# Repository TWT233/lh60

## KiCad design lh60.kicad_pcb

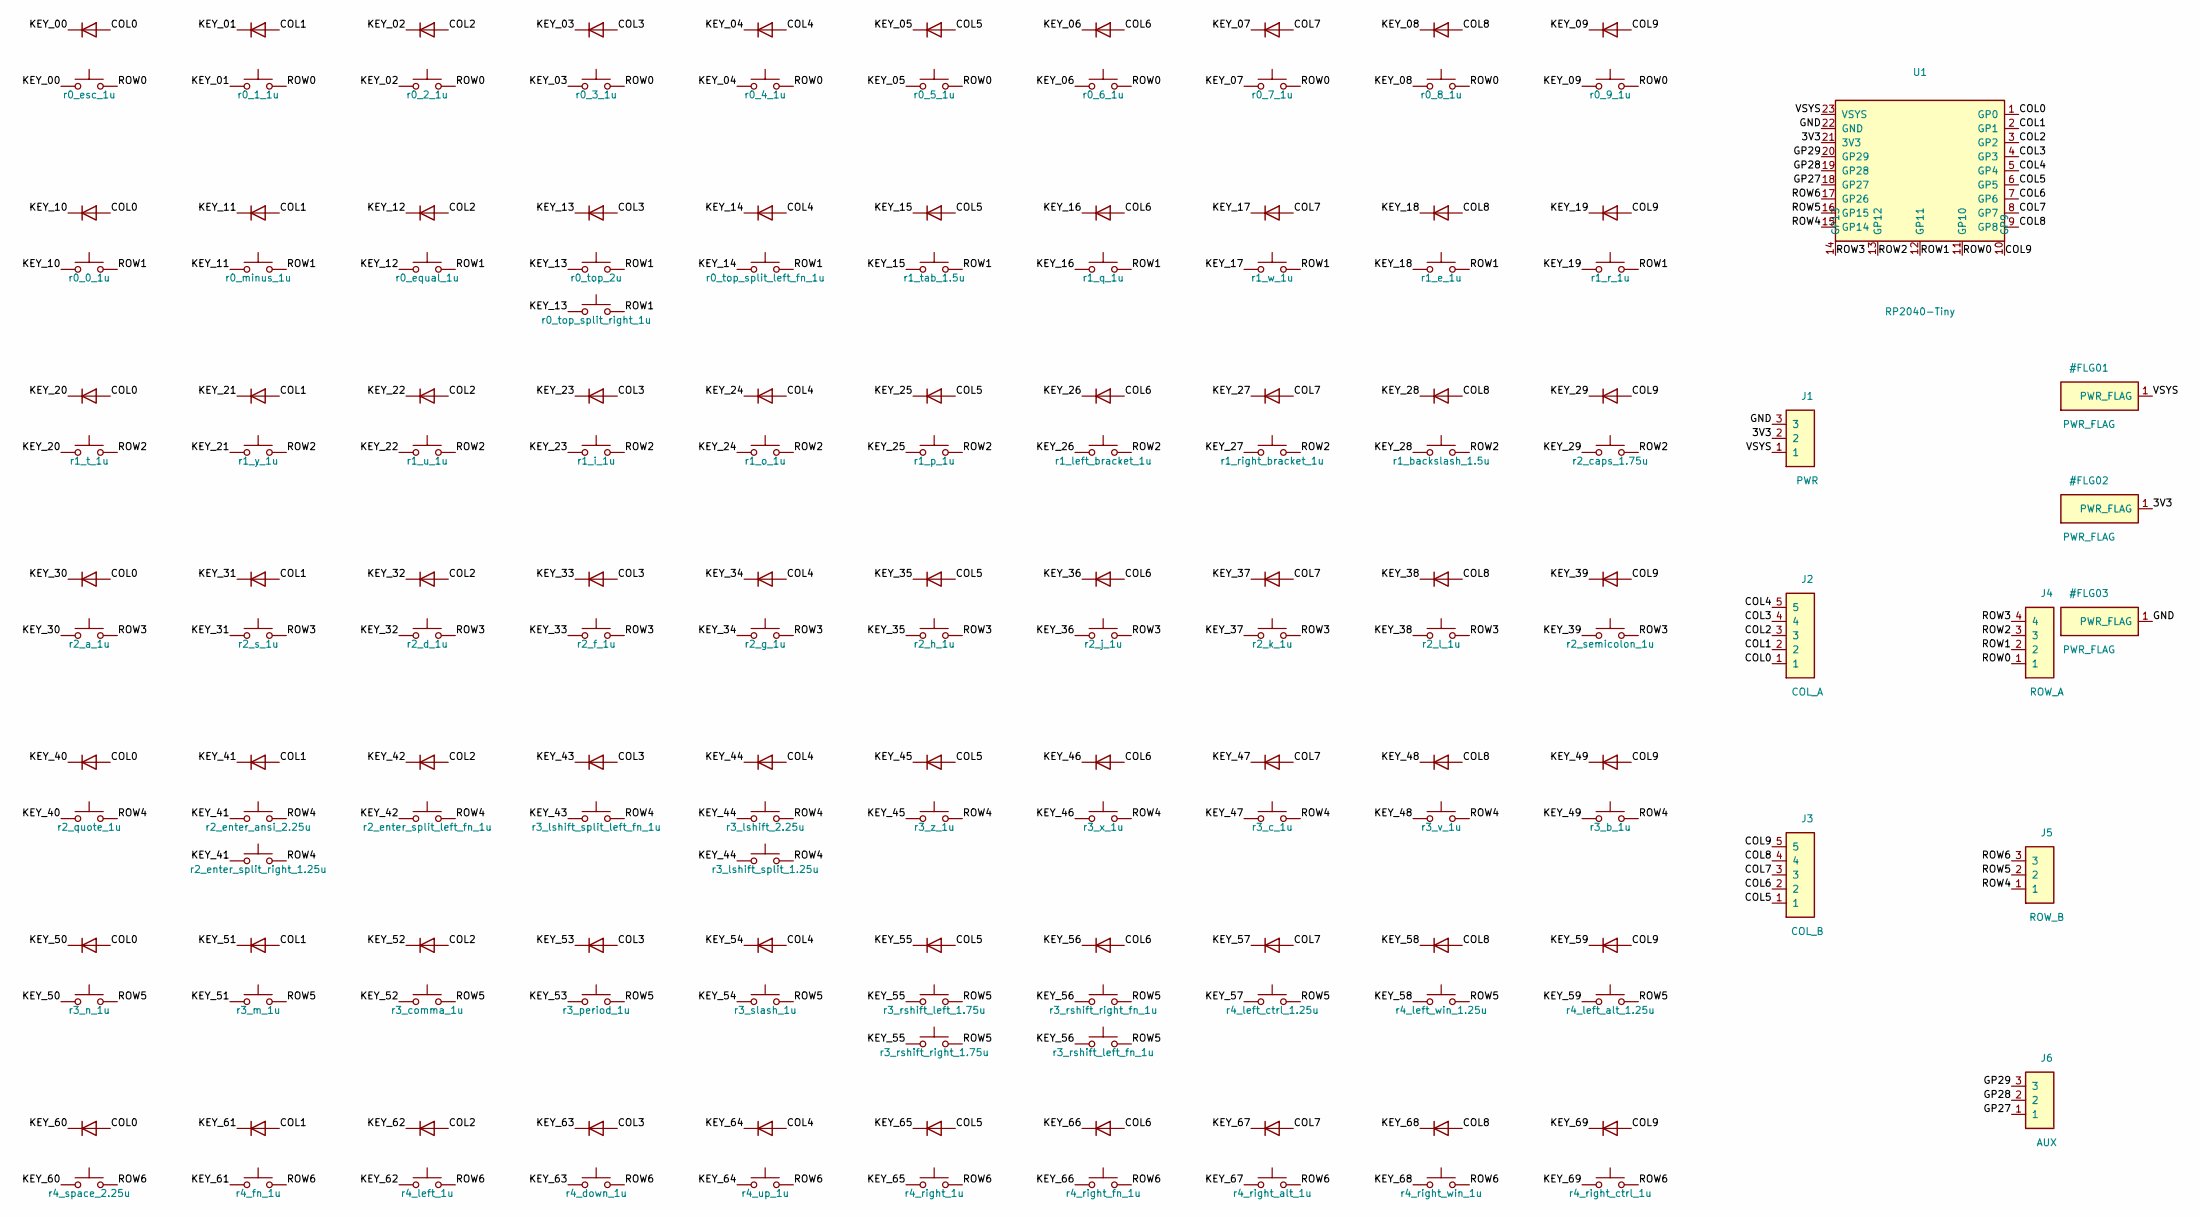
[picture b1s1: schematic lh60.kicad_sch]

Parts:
D1, D2, D3, D4, D5, D6, D7, D8, D9, D10, D11, D12, D13, D14, D15, D16, D17, D18, D19, D20, D21, D22, D23, D24, D25, D26, D27, D28, D29, D30, D31, D32, D33, D34, D35, D36, D37, D38, D39, D40, D41, D42, D43, D44, D45, D46, D47, D48, D49, D50, D51, D52, D53, D54, D55, D56, D57, D58, D59, D60, D61, D62, D63, D64, D65, D66, D67, D68, D69, D70: 1N4148WS; D_SOD-323_Bottom
J1: PWR; PinHeader_1x03_P2.54mm_Vertical
J2: COL_A; PinHeader_1x05_P2.54mm_Vertical
J3: COL_B; PinHeader_1x05_P2.54mm_Vertical
J4: ROW_A; PinHeader_1x04_P2.54mm_Vertical
J5: ROW_B; PinHeader_1x03_P2.54mm_Vertical
J6: AUX; PinHeader_1x03_P2.54mm_Vertical
SW1: r0_esc_1u; Gateron-LP-or-ChocV1-Hotswap-Socket-1U
SW2: r0_1_1u; Gateron-LP-or-ChocV1-Hotswap-Socket-1U
SW3: r0_2_1u; Gateron-LP-or-ChocV1-Hotswap-Socket-1U
SW4: r0_3_1u; Gateron-LP-or-ChocV1-Hotswap-Socket-1U
SW5: r0_4_1u; Gateron-LP-or-ChocV1-Hotswap-Socket-1U
SW6: r0_5_1u; Gateron-LP-or-ChocV1-Hotswap-Socket-1U
SW7: r0_6_1u; Gateron-LP-or-ChocV1-Hotswap-Socket-1U
SW8: r0_7_1u; Gateron-LP-or-ChocV1-Hotswap-Socket-1U
SW9: r0_8_1u; Gateron-LP-or-ChocV1-Hotswap-Socket-1U
SW10: r0_9_1u; Gateron-LP-or-ChocV1-Hotswap-Socket-1U
SW11: r0_0_1u; Gateron-LP-or-ChocV1-Hotswap-Socket-1U
SW12: r0_minus_1u; Gateron-LP-or-ChocV1-Hotswap-Socket-1U
SW13: r0_equal_1u; Gateron-LP-or-ChocV1-Hotswap-Socket-1U
SW14: r0_top_2u; Gateron-LP-Hotswap-Socket-2U
SW15: r0_top_split_left_fn_1u; Gateron-LP-Hotswap-Socket-1U
SW16: r0_top_split_right_1u; Gateron-LP-Hotswap-Socket-1U
SW17: r1_tab_1.5u; Gateron-LP-or-ChocV1-Hotswap-Socket-1.5U
SW18: r1_q_1u; Gateron-LP-or-ChocV1-Hotswap-Socket-1U
SW19: r1_w_1u; Gateron-LP-or-ChocV1-Hotswap-Socket-1U
SW20: r1_e_1u; Gateron-LP-or-ChocV1-Hotswap-Socket-1U
SW21: r1_r_1u; Gateron-LP-or-ChocV1-Hotswap-Socket-1U
SW22: r1_t_1u; Gateron-LP-or-ChocV1-Hotswap-Socket-1U
SW23: r1_y_1u; Gateron-LP-or-ChocV1-Hotswap-Socket-1U
SW24: r1_u_1u; Gateron-LP-or-ChocV1-Hotswap-Socket-1U
SW25: r1_i_1u; Gateron-LP-or-ChocV1-Hotswap-Socket-1U
SW26: r1_o_1u; Gateron-LP-or-ChocV1-Hotswap-Socket-1U
SW27: r1_p_1u; Gateron-LP-or-ChocV1-Hotswap-Socket-1U
SW28: r1_left_bracket_1u; Gateron-LP-or-ChocV1-Hotswap-Socket-1U
SW29: r1_right_bracket_1u; Gateron-LP-or-ChocV1-Hotswap-Socket-1U
SW30: r1_backslash_1.5u; Gateron-LP-or-ChocV1-Hotswap-Socket-1.5U
SW31: r2_caps_1.75u; Gateron-LP-or-ChocV1-Hotswap-Socket-1.75U
SW32: r2_a_1u; Gateron-LP-or-ChocV1-Hotswap-Socket-1U
SW33: r2_s_1u; Gateron-LP-or-ChocV1-Hotswap-Socket-1U
SW34: r2_d_1u; Gateron-LP-or-ChocV1-Hotswap-Socket-1U
SW35: r2_f_1u; Gateron-LP-or-ChocV1-Hotswap-Socket-1U
SW36: r2_g_1u; Gateron-LP-or-ChocV1-Hotswap-Socket-1U
SW37: r2_h_1u; Gateron-LP-or-ChocV1-Hotswap-Socket-1U
SW38: r2_j_1u; Gateron-LP-or-ChocV1-Hotswap-Socket-1U
SW39: r2_k_1u; Gateron-LP-or-ChocV1-Hotswap-Socket-1U
SW40: r2_l_1u; Gateron-LP-or-ChocV1-Hotswap-Socket-1U
SW41: r2_semicolon_1u; Gateron-LP-or-ChocV1-Hotswap-Socket-1U
SW42: r2_quote_1u; Gateron-LP-or-ChocV1-Hotswap-Socket-1U
SW43: r2_enter_ansi_2.25u; Gateron-LP-Hotswap-Socket-2.25U
SW44: r2_enter_split_left_fn_1u; Gateron-LP-Hotswap-Socket-1U
SW45: r2_enter_split_right_1.25u; Gateron-LP-Hotswap-Socket-1.25U
SW46: r3_lshift_split_left_fn_1u; Gateron-LP-Hotswap-Socket-1U
SW47: r3_lshift_2.25u; Gateron-LP-Hotswap-Socket-2.25U
SW48: r3_lshift_split_1.25u; Gateron-LP-Hotswap-Socket-1.25U
SW49: r3_z_1u; Gateron-LP-or-ChocV1-Hotswap-Socket-1U
SW50: r3_x_1u; Gateron-LP-or-ChocV1-Hotswap-Socket-1U
SW51: r3_c_1u; Gateron-LP-or-ChocV1-Hotswap-Socket-1U
SW52: r3_v_1u; Gateron-LP-or-ChocV1-Hotswap-Socket-1U
SW53: r3_b_1u; Gateron-LP-or-ChocV1-Hotswap-Socket-1U
SW54: r3_n_1u; Gateron-LP-or-ChocV1-Hotswap-Socket-1U
SW55: r3_m_1u; Gateron-LP-or-ChocV1-Hotswap-Socket-1U
SW56: r3_comma_1u; Gateron-LP-or-ChocV1-Hotswap-Socket-1U
SW57: r3_period_1u; Gateron-LP-or-ChocV1-Hotswap-Socket-1U
SW58: r3_slash_1u; Gateron-LP-or-ChocV1-Hotswap-Socket-1U
SW60: r3_rshift_left_1.75u; Gateron-LP-Hotswap-Socket-1.75U
SW61: r3_rshift_right_fn_1u; Gateron-LP-Hotswap-Socket-1U
SW62: r3_rshift_left_fn_1u; Gateron-LP-Hotswap-Socket-1U
SW63: r3_rshift_right_1.75u; Gateron-LP-Hotswap-Socket-1.75U
SW64: r4_left_ctrl_1.25u; Gateron-LP-or-ChocV1-Hotswap-Socket-1.25U
SW65: r4_left_win_1.25u; Gateron-LP-or-ChocV1-Hotswap-Socket-1.25U
SW66: r4_left_alt_1.25u; Gateron-LP-or-ChocV1-Hotswap-Socket-1.25U
SW67: r4_space_2.25u; Gateron-LP-or-ChocV1-Hotswap-Socket-2.25U
SW68: r4_fn_1u; Gateron-LP-or-ChocV1-Hotswap-Socket-1U
SW69: r4_left_1u; Gateron-LP-or-ChocV1-Hotswap-Socket-1U
SW70: r4_down_1u; Gateron-LP-or-ChocV1-Hotswap-Socket-1U
SW71: r4_up_1u; Gateron-LP-or-ChocV1-Hotswap-Socket-1U
SW72: r4_right_1u; Gateron-LP-or-ChocV1-Hotswap-Socket-1U
SW73: r4_right_fn_1u; Gateron-LP-or-ChocV1-Hotswap-Socket-1U
SW74: r4_right_alt_1u; Gateron-LP-or-ChocV1-Hotswap-Socket-1U
SW75: r4_right_win_1u; Gateron-LP-or-ChocV1-Hotswap-Socket-1U
SW76: r4_right_ctrl_1u; Gateron-LP-or-ChocV1-Hotswap-Socket-1U
U1: RP2040-Tiny; MCU_RP2040-Tiny_SMD

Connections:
/3V3: J1.2, U1.21 (3V3)
/COL0: D1.2 (A), D11.2 (A), D21.2 (A), D31.2 (A), D41.2 (A), D51.2 (A), D61.2 (A), J2.1, U1.1 (GP0)
/COL1: D2.2 (A), D12.2 (A), D22.2 (A), D32.2 (A), D42.2 (A), D52.2 (A), D62.2 (A), J2.2, U1.2 (GP1)
/COL2: D3.2 (A), D13.2 (A), D23.2 (A), D33.2 (A), D43.2 (A), D53.2 (A), D63.2 (A), J2.3, U1.3 (GP2)
/COL3: D4.2 (A), D14.2 (A), D24.2 (A), D34.2 (A), D44.2 (A), D54.2 (A), D64.2 (A), J2.4, U1.4 (GP3)
/COL4: D5.2 (A), D15.2 (A), D25.2 (A), D35.2 (A), D45.2 (A), D55.2 (A), D65.2 (A), J2.5, U1.5 (GP4)
/COL5: D6.2 (A), D16.2 (A), D26.2 (A), D36.2 (A), D46.2 (A), D56.2 (A), D66.2 (A), J3.1, U1.6 (GP5)
/COL6: D7.2 (A), D17.2 (A), D27.2 (A), D37.2 (A), D47.2 (A), D57.2 (A), D67.2 (A), J3.2, U1.7 (GP6)
/COL7: D8.2 (A), D18.2 (A), D28.2 (A), D38.2 (A), D48.2 (A), D58.2 (A), D68.2 (A), J3.3, U1.8 (GP7)
/COL8: D9.2 (A), D19.2 (A), D29.2 (A), D39.2 (A), D49.2 (A), D59.2 (A), D69.2 (A), J3.4, U1.9 (GP8)
/COL9: D10.2 (A), D20.2 (A), D30.2 (A), D40.2 (A), D50.2 (A), D60.2 (A), D70.2 (A), J3.5, U1.10 (GP9)
/GND: J1.3, U1.22 (GND)
/GP27: J6.1, U1.18 (GP27)
/GP28: J6.2, U1.19 (GP28)
/GP29: J6.3, U1.20 (GP29)
/KEY_00: D1.1 (K), SW1.1
/KEY_01: D2.1 (K), SW2.1
/KEY_02: D3.1 (K), SW3.1
/KEY_03: D4.1 (K), SW4.1
/KEY_04: D5.1 (K), SW5.1
/KEY_05: D6.1 (K), SW6.1
/KEY_06: D7.1 (K), SW7.1
/KEY_07: D8.1 (K), SW8.1
/KEY_08: D9.1 (K), SW9.1
/KEY_09: D10.1 (K), SW10.1
/KEY_10: D11.1 (K), SW11.1
/KEY_11: D12.1 (K), SW12.1
/KEY_12: D13.1 (K), SW13.1
/KEY_13: D14.1 (K), SW14.1, SW16.1
/KEY_14: D15.1 (K), SW15.1
/KEY_15: D16.1 (K), SW17.1
/KEY_16: D17.1 (K), SW18.1
/KEY_17: D18.1 (K), SW19.1
/KEY_18: D19.1 (K), SW20.1
/KEY_19: D20.1 (K), SW21.1
/KEY_20: D21.1 (K), SW22.1
/KEY_21: D22.1 (K), SW23.1
/KEY_22: D23.1 (K), SW24.1
/KEY_23: D24.1 (K), SW25.1
/KEY_24: D25.1 (K), SW26.1
/KEY_25: D26.1 (K), SW27.1
/KEY_26: D27.1 (K), SW28.1
/KEY_27: D28.1 (K), SW29.1
/KEY_28: D29.1 (K), SW30.1
/KEY_29: D30.1 (K), SW31.1
/KEY_30: D31.1 (K), SW32.1
/KEY_31: D32.1 (K), SW33.1
/KEY_32: D33.1 (K), SW34.1
/KEY_33: D34.1 (K), SW35.1
/KEY_34: D35.1 (K), SW36.1
/KEY_35: D36.1 (K), SW37.1
/KEY_36: D37.1 (K), SW38.1
/KEY_37: D38.1 (K), SW39.1
/KEY_38: D39.1 (K), SW40.1
/KEY_39: D40.1 (K), SW41.1
/KEY_40: D41.1 (K), SW42.1
/KEY_41: D42.1 (K), SW43.1, SW45.1
/KEY_42: D43.1 (K), SW44.1
/KEY_43: D44.1 (K), SW46.1
/KEY_44: D45.1 (K), SW47.1, SW48.1
/KEY_45: D46.1 (K), SW49.1
/KEY_46: D47.1 (K), SW50.1
/KEY_47: D48.1 (K), SW51.1
/KEY_48: D49.1 (K), SW52.1
/KEY_49: D50.1 (K), SW53.1
/KEY_50: D51.1 (K), SW54.1
/KEY_51: D52.1 (K), SW55.1
/KEY_52: D53.1 (K), SW56.1
/KEY_53: D54.1 (K), SW57.1
/KEY_54: D55.1 (K), SW58.1
/KEY_55: D56.1 (K), SW60.1, SW63.1
/KEY_56: D57.1 (K), SW61.1, SW62.1
/KEY_57: D58.1 (K), SW64.1
/KEY_58: D59.1 (K), SW65.1
/KEY_59: D60.1 (K), SW66.1
/KEY_60: D61.1 (K), SW67.1
/KEY_61: D62.1 (K), SW68.1
/KEY_62: D63.1 (K), SW69.1
/KEY_63: D64.1 (K), SW70.1
/KEY_64: D65.1 (K), SW71.1
/KEY_65: D66.1 (K), SW72.1
/KEY_66: D67.1 (K), SW73.1
/KEY_67: D68.1 (K), SW74.1
/KEY_68: D69.1 (K), SW75.1
/KEY_69: D70.1 (K), SW76.1
/ROW0: J4.1, SW1.2, SW2.2, SW3.2, SW4.2, SW5.2, SW6.2, SW7.2, SW8.2, SW9.2, SW10.2, U1.11 (GP10)
/ROW1: J4.2, SW11.2, SW12.2, SW13.2, SW14.2, SW15.2, SW16.2, SW17.2, SW18.2, SW19.2, SW20.2, SW21.2, U1.12 (GP11)
/ROW2: J4.3, SW22.2, SW23.2, SW24.2, SW25.2, SW26.2, SW27.2, SW28.2, SW29.2, SW30.2, SW31.2, U1.13 (GP12)
/ROW3: J4.4, SW32.2, SW33.2, SW34.2, SW35.2, SW36.2, SW37.2, SW38.2, SW39.2, SW40.2, SW41.2, U1.14 (GP13)
/ROW4: J5.1, SW42.2, SW43.2, SW44.2, SW45.2, SW46.2, SW47.2, SW48.2, SW49.2, SW50.2, SW51.2, SW52.2, SW53.2, U1.15 (GP14)
/ROW5: J5.2, SW54.2, SW55.2, SW56.2, SW57.2, SW58.2, SW60.2, SW61.2, SW62.2, SW63.2, SW64.2, SW65.2, SW66.2, U1.16 (GP15)
/ROW6: J5.3, SW67.2, SW68.2, SW69.2, SW70.2, SW71.2, SW72.2, SW73.2, SW74.2, SW75.2, SW76.2, U1.17 (GP26)
/VSYS: J1.1, U1.23 (VSYS)

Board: 2 copper layers, 152 parts (6 on the bottom side), 93 nets, no tracks yet.

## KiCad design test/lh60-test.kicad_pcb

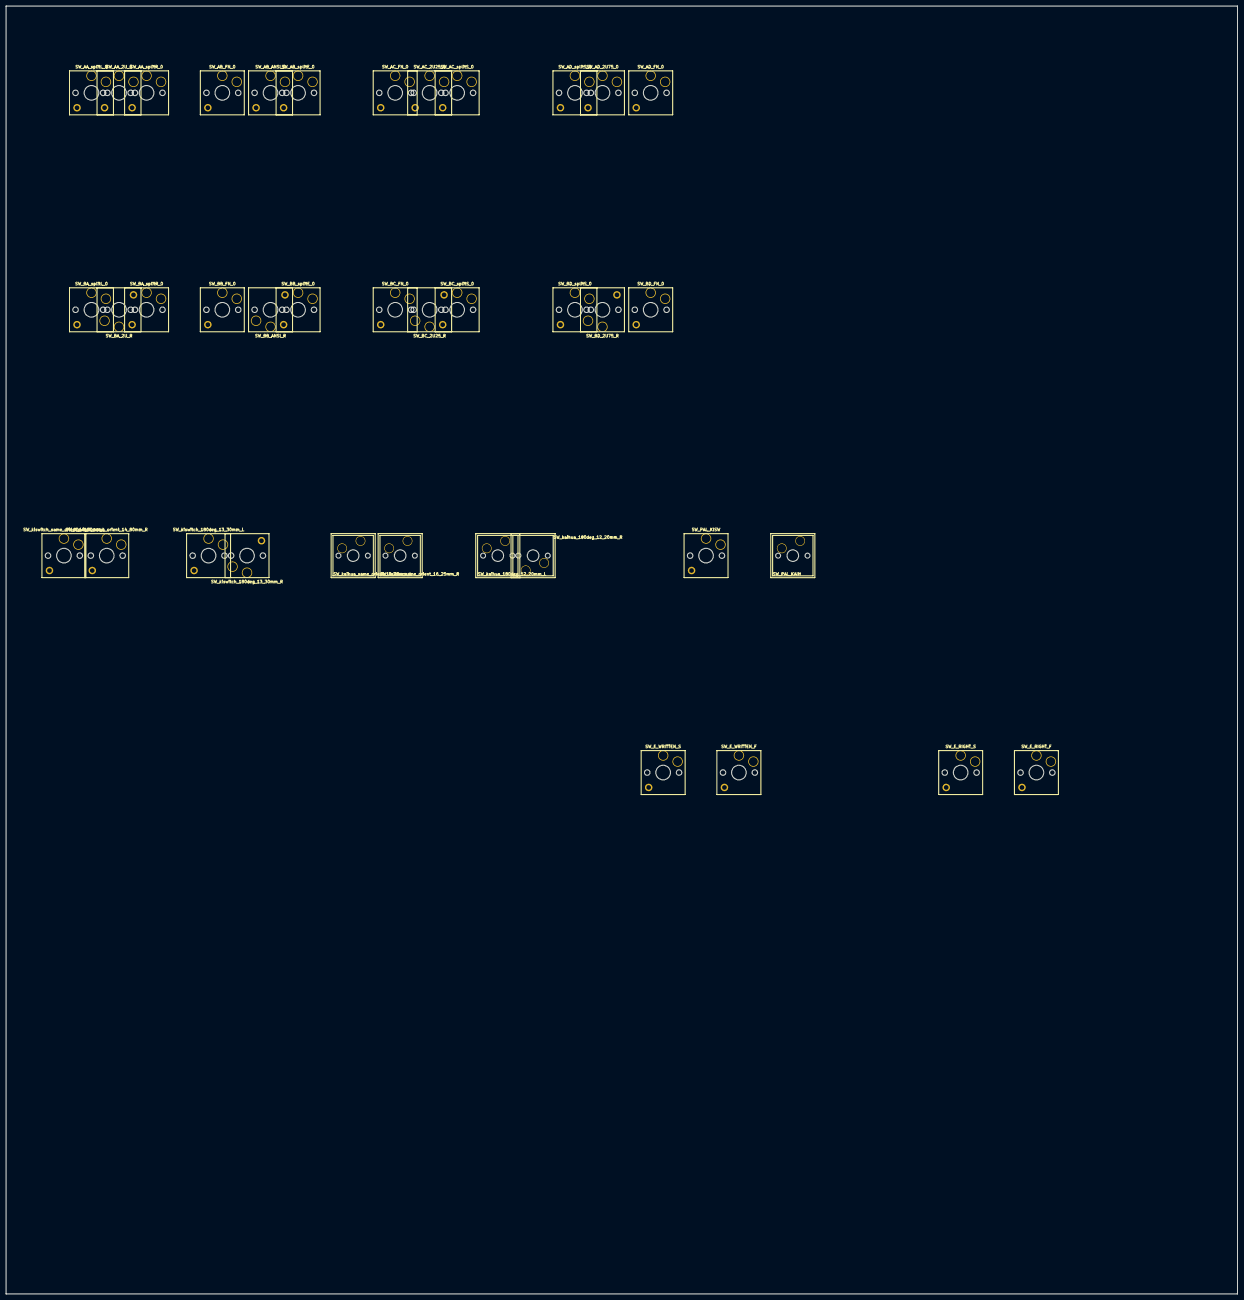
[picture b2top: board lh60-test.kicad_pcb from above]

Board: 2 copper layers, 425.8 x 445.2 mm, 38 parts (0 on the bottom side), 38 nets, no tracks yet.

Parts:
SW_AA_2U_0: SW_Hotswap_Kailh_Choc_V1V2_Plated_1.00u; test
SW_AA_splitL_0: SW_Hotswap_Kailh_Choc_V1V2_Plated_1.00u; test
SW_AA_splitR_0: SW_Hotswap_Kailh_Choc_V1V2_Plated_1.00u; test
SW_AB_ANSI_0: SW_Hotswap_Kailh_Choc_V1V2_Plated_1.00u; test
SW_AB_FN_0: SW_Hotswap_Kailh_Choc_V1V2_Plated_1.00u; test
SW_AB_splitE_0: SW_Hotswap_Kailh_Choc_V1V2_Plated_1.00u; test
SW_AC_2U25_0: SW_Hotswap_Kailh_Choc_V1V2_Plated_1.00u; test
SW_AC_FN_0: SW_Hotswap_Kailh_Choc_V1V2_Plated_1.00u; test
SW_AC_splitS_0: SW_Hotswap_Kailh_Choc_V1V2_Plated_1.00u; test
SW_AD_2U75_0: SW_Hotswap_Kailh_Choc_V1V2_Plated_1.00u; test
SW_AD_FN_0: SW_Hotswap_Kailh_Choc_V1V2_Plated_1.00u; test
SW_AD_splitS_0: SW_Hotswap_Kailh_Choc_V1V2_Plated_1.00u; test
SW_BA_2U_R: SW_Hotswap_Kailh_Choc_V1V2_Plated_1.00u; test
SW_BA_splitL_0: SW_Hotswap_Kailh_Choc_V1V2_Plated_1.00u; test
SW_BA_splitR_0: SW_Hotswap_Kailh_Choc_V1V2_Plated_1.00u; test
SW_BB_ANSI_R: SW_Hotswap_Kailh_Choc_V1V2_Plated_1.00u; test
SW_BB_FN_0: SW_Hotswap_Kailh_Choc_V1V2_Plated_1.00u; test
SW_BB_splitE_0: SW_Hotswap_Kailh_Choc_V1V2_Plated_1.00u; test
SW_BC_2U25_R: SW_Hotswap_Kailh_Choc_V1V2_Plated_1.00u; test
SW_BC_FN_0: SW_Hotswap_Kailh_Choc_V1V2_Plated_1.00u; test
SW_BC_splitS_0: SW_Hotswap_Kailh_Choc_V1V2_Plated_1.00u; test
SW_BD_2U75_R: SW_Hotswap_Kailh_Choc_V1V2_Plated_1.00u; test
SW_BD_FN_0: SW_Hotswap_Kailh_Choc_V1V2_Plated_1.00u; test
SW_BD_splitS_0: SW_Hotswap_Kailh_Choc_V1V2_Plated_1.00u; test
SW_E_RIGHT_F: SW_Hotswap_Kailh_Choc_V1V2_Plated_1.00u; test
SW_E_RIGHT_S: SW_Hotswap_Kailh_Choc_V1V2_Plated_1.00u; test
SW_E_WRITTEN_F: SW_Hotswap_Kailh_Choc_V1V2_Plated_1.00u; test
SW_E_WRITTEN_S: SW_Hotswap_Kailh_Choc_V1V2_Plated_1.00u; test
SW_PAL_KAIH: SW; KaiHua_Contact_1.00u
SW_PAL_KISW: SW_Hotswap_Kailh_Choc_V1V2_Plated_1.00u; test
SW_kaihua_180deg_12_20mm_L, SW_kaihua_180deg_12_20mm_R: SW; KaiHua_Contact_1.00u
SW_kaihua_same_orient_16_25mm_L, SW_kaihua_same_orient_16_25mm_R: SW; KaiHua_Contact_1.00u
SW_kiswitch_180deg_13_30mm_L, SW_kiswitch_180deg_13_30mm_R: SW_Hotswap_Kailh_Choc_V1V2_Plated_1.00u; test
SW_kiswitch_same_orient_14_80mm_L, SW_kiswitch_same_orient_14_80mm_R: SW_Hotswap_Kailh_Choc_V1V2_Plated_1.00u; test

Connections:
N1: SW_AA_2U_0.1, SW_AA_2U_0.2
N2: SW_AA_splitL_0.1, SW_AA_splitL_0.2
N3: SW_AA_splitR_0.1, SW_AA_splitR_0.2
N4: SW_AB_ANSI_0.1, SW_AB_ANSI_0.2
N5: SW_AB_FN_0.1, SW_AB_FN_0.2
N6: SW_AB_splitE_0.1, SW_AB_splitE_0.2
N7: SW_AC_2U25_0.1, SW_AC_2U25_0.2
N8: SW_AC_FN_0.1, SW_AC_FN_0.2
N9: SW_AC_splitS_0.1, SW_AC_splitS_0.2
N10: SW_AD_2U75_0.1, SW_AD_2U75_0.2
N11: SW_AD_splitS_0.1, SW_AD_splitS_0.2
N12: SW_AD_FN_0.1, SW_AD_FN_0.2
N13: SW_BA_2U_R.1, SW_BA_2U_R.2
N14: SW_BA_splitL_0.1, SW_BA_splitL_0.2
N15: SW_BA_splitR_0.1, SW_BA_splitR_0.2
N16: SW_BB_ANSI_R.1, SW_BB_ANSI_R.2
N17: SW_BB_FN_0.1, SW_BB_FN_0.2
N18: SW_BB_splitE_0.1, SW_BB_splitE_0.2
N19: SW_BC_2U25_R.1, SW_BC_2U25_R.2
N20: SW_BC_FN_0.1, SW_BC_FN_0.2
N21: SW_BC_splitS_0.1, SW_BC_splitS_0.2
N22: SW_BD_2U75_R.1, SW_BD_2U75_R.2
N23: SW_BD_splitS_0.1, SW_BD_splitS_0.2
N24: SW_BD_FN_0.1, SW_BD_FN_0.2
N25: SW_kiswitch_same_orient_14_80mm_L.1, SW_kiswitch_same_orient_14_80mm_L.2
N26: SW_kiswitch_same_orient_14_80mm_R.1, SW_kiswitch_same_orient_14_80mm_R.2
N27: SW_kiswitch_180deg_13_30mm_L.1, SW_kiswitch_180deg_13_30mm_L.2
N28: SW_kiswitch_180deg_13_30mm_R.1, SW_kiswitch_180deg_13_30mm_R.2
N29: SW_kaihua_same_orient_16_25mm_L.1, SW_kaihua_same_orient_16_25mm_L.2
N30: SW_kaihua_same_orient_16_25mm_R.1, SW_kaihua_same_orient_16_25mm_R.2
N31: SW_kaihua_180deg_12_20mm_L.1, SW_kaihua_180deg_12_20mm_L.2
N32: SW_kaihua_180deg_12_20mm_R.1, SW_kaihua_180deg_12_20mm_R.2
N33: SW_PAL_KISW.1, SW_PAL_KISW.2
N34: SW_PAL_KAIH.1, SW_PAL_KAIH.2
N35: SW_E_WRITTEN_S.1, SW_E_WRITTEN_S.2
N36: SW_E_WRITTEN_F.1, SW_E_WRITTEN_F.2
N37: SW_E_RIGHT_S.1, SW_E_RIGHT_S.2
N38: SW_E_RIGHT_F.1, SW_E_RIGHT_F.2

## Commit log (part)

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2022-03-10 feat: init
2022-03-10 chore: trunk commit
2022-03-11 20220311
2022-03-13 20220313
2022-03-25 20220325 atmega->stm32
2022-03-25 sch fin
2022-03-26 20220326 pcb init
2022-03-26 20220326 pcb: keycap mount
2022-03-26 20220326 fin
2022-03-29 20220329 finish pcb
2022-04-01 20220401 sch 2.0
2023-08-19 alter usbc to jump connecter
2023-08-20 finish pcb v2
2023-08-20 fix: hole colli
2023-08-24 ds store
